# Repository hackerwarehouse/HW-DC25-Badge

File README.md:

# HW-DC25-Badge

This is the project page for the Hacker Warehouse electronic badge that was made for DEF CON 25.

## Background / timeline of badge development

* This was our first attempt at custom hardware / any electronics project at a larger scale
* 2 hardware revisions, 1 silkscreen revision = 3 prototype runs = 4-5 months
* After final board design was obtained, coding started (all code prior was test code to ensure components were working)
* 2 week code sprint before code needed to be frozen for mass badge flashing
* All boards flashed / all components obtained the week of travel of Las Vegas (one final box arrived the day prior to leaving which gave me some anxiety as well)
* 425 badges were produced 

## Badge Specs

* 96×64 Graphic Full Color OLED Display
* 14x Mini NeoPixel RGB LEDs
* ESP8266EX
* 4 tactile buttons arranged in Joypad configuration
* 8 MB Storage
* Powered via 2 AA batteries

## Badge Functions:

* 802.11 channel activity monitor
* Access point scanner
* LED patterns
* OLED animations
* Personalization
* Other useful network tools

## Release Notes
* There was debate if any/all the mischief tools should be included in the badge by default, include it but have them keycode unlockable, or just not include it in stock firmware. Because we know the people working on/in the Black Hat and DEF CON network, along with wanting to have a usable network without causing more issues, the features were not included. 
  * The continued usage of the word 'locked' in all areas made people assume it was all unlockable during the con. We should have chosen different words for the various areas of inclusion. Sorry about that. 

* Multiple reports during DEF CON on wifi functions not working after x usage. Originally suspected it was the sleep/wakeup or disconnect functions not being triggered properly but that doesn't seem to be it. 
  * As previously mentioned, all the badge software was in a two week sprint which didn't leave much or any time for debugging 

* We originally stated source/binaries would be released after the con but because of wifi bug we were wanting to debug and fix it prior to first public release. It seems like people want the code first so we are releasing it as is with the hopes more eyes on it the better and fixes can be submitted. 

## Compiling

These instructions will get you a copy of the project up and running on your local machine.

### Prerequisites

What things you need to install the software and how to install them

```
1. Arduino / compiler
2. Libraries via package manager
  https://github.com/esp8266/Arduino -> http://arduino.esp8266.com/versions/2.3.0/package_esp8266com_index.json
  https://github.com/adafruit/Adafruit_NeoPixel
  https://github.com/kitesurfer1404/WS2812FX
3. Manually copy the two other library packages to Arduino libraries folder
4. 3.3v serial cable
5. and of course a Hacker Warehouse DC25 Badge
```

### Uploading firmware to badge

1. Press / hold the up button on badge
2. Connect 3.3v serial cable
3. Use arduino compile to upload or use other methods such as esptool or esp8266_flasher (with binary file)
  * 115200

## Authors / Contributors

* **Garrett Gee**
* **Jaycon Systems**

## Acknowledgments

* Hat tip to anyone who's code was used
* All the supporters of this project
*

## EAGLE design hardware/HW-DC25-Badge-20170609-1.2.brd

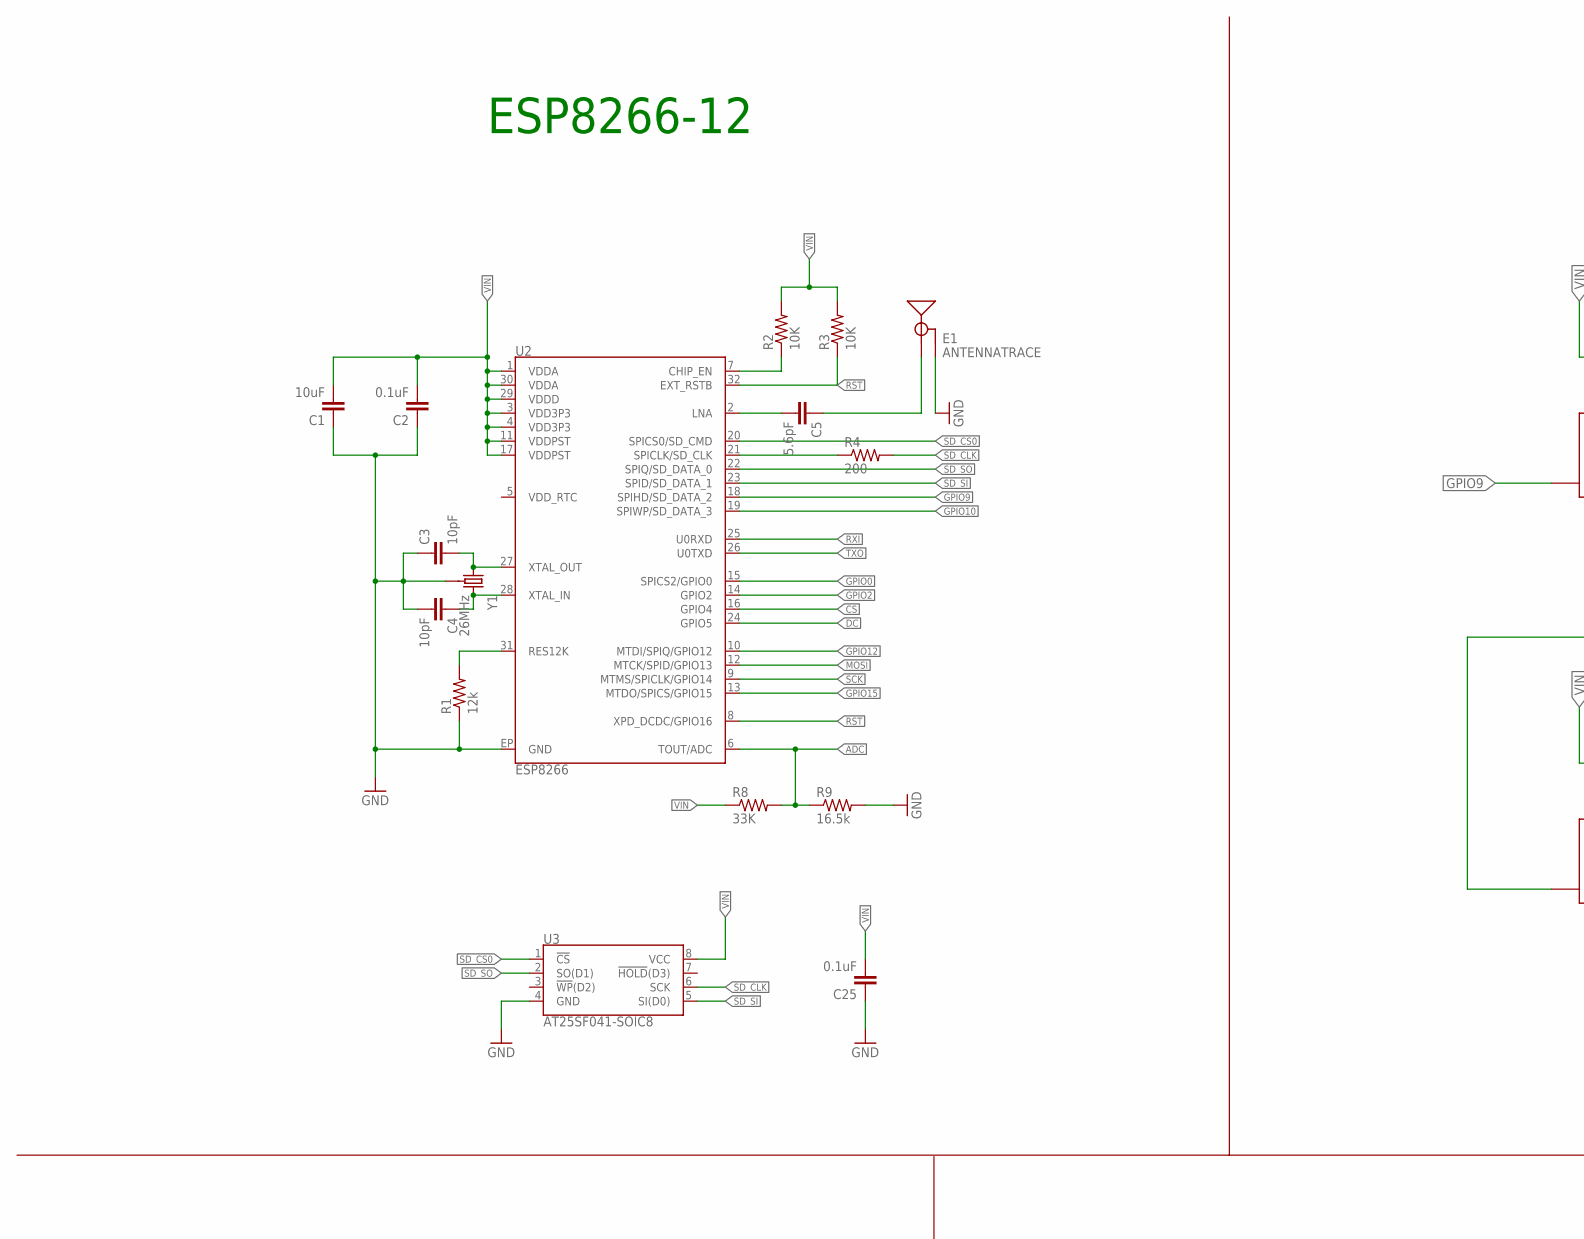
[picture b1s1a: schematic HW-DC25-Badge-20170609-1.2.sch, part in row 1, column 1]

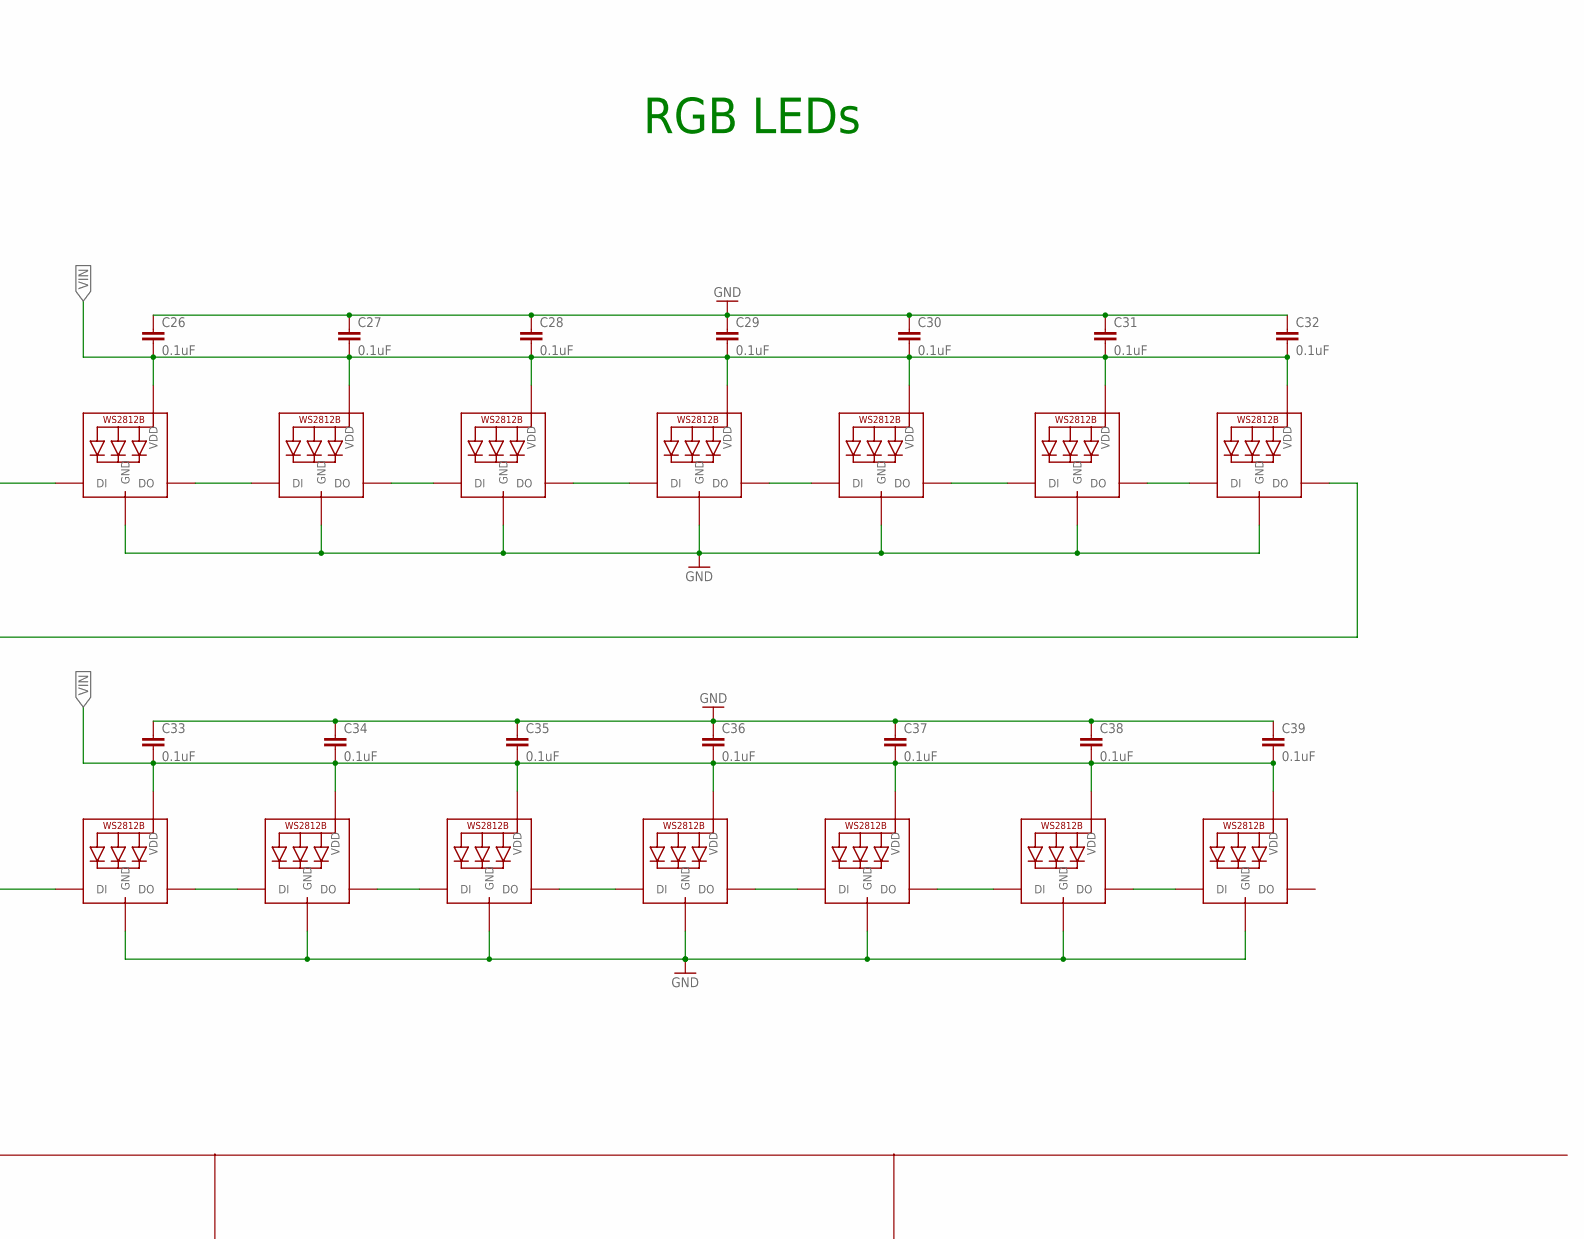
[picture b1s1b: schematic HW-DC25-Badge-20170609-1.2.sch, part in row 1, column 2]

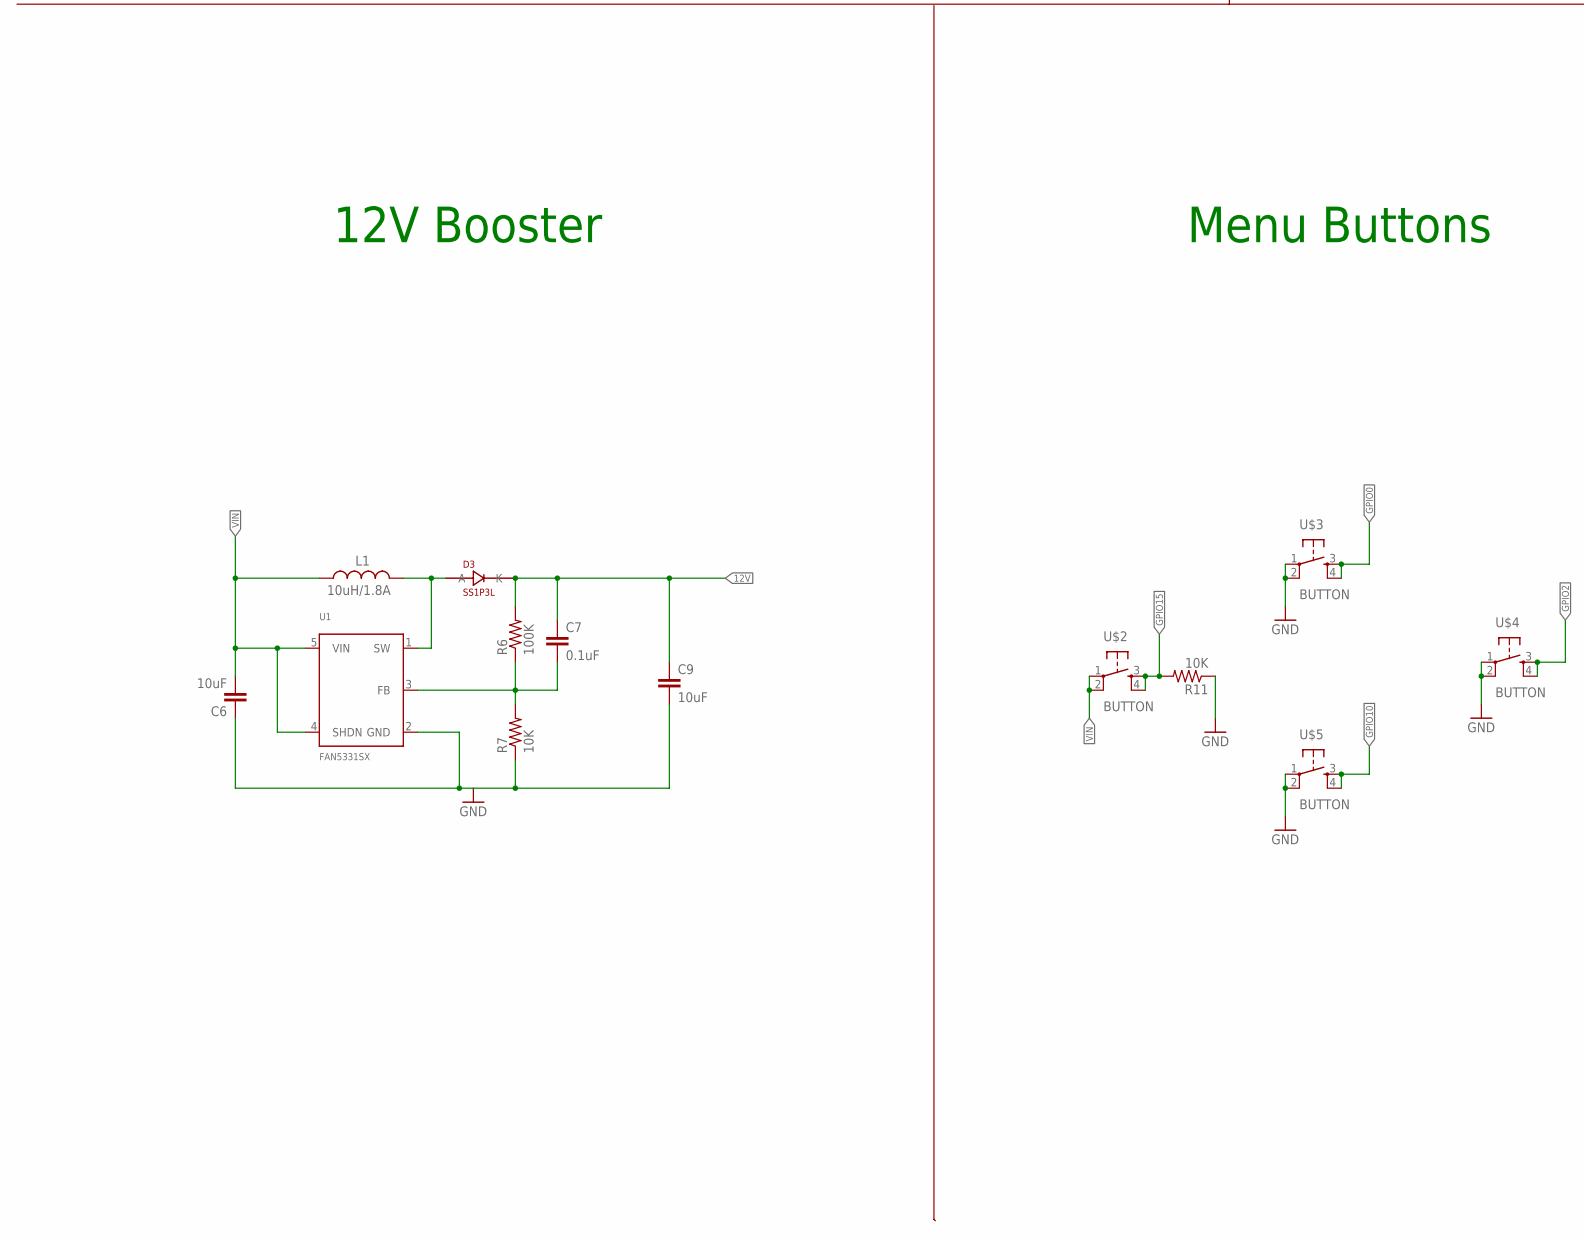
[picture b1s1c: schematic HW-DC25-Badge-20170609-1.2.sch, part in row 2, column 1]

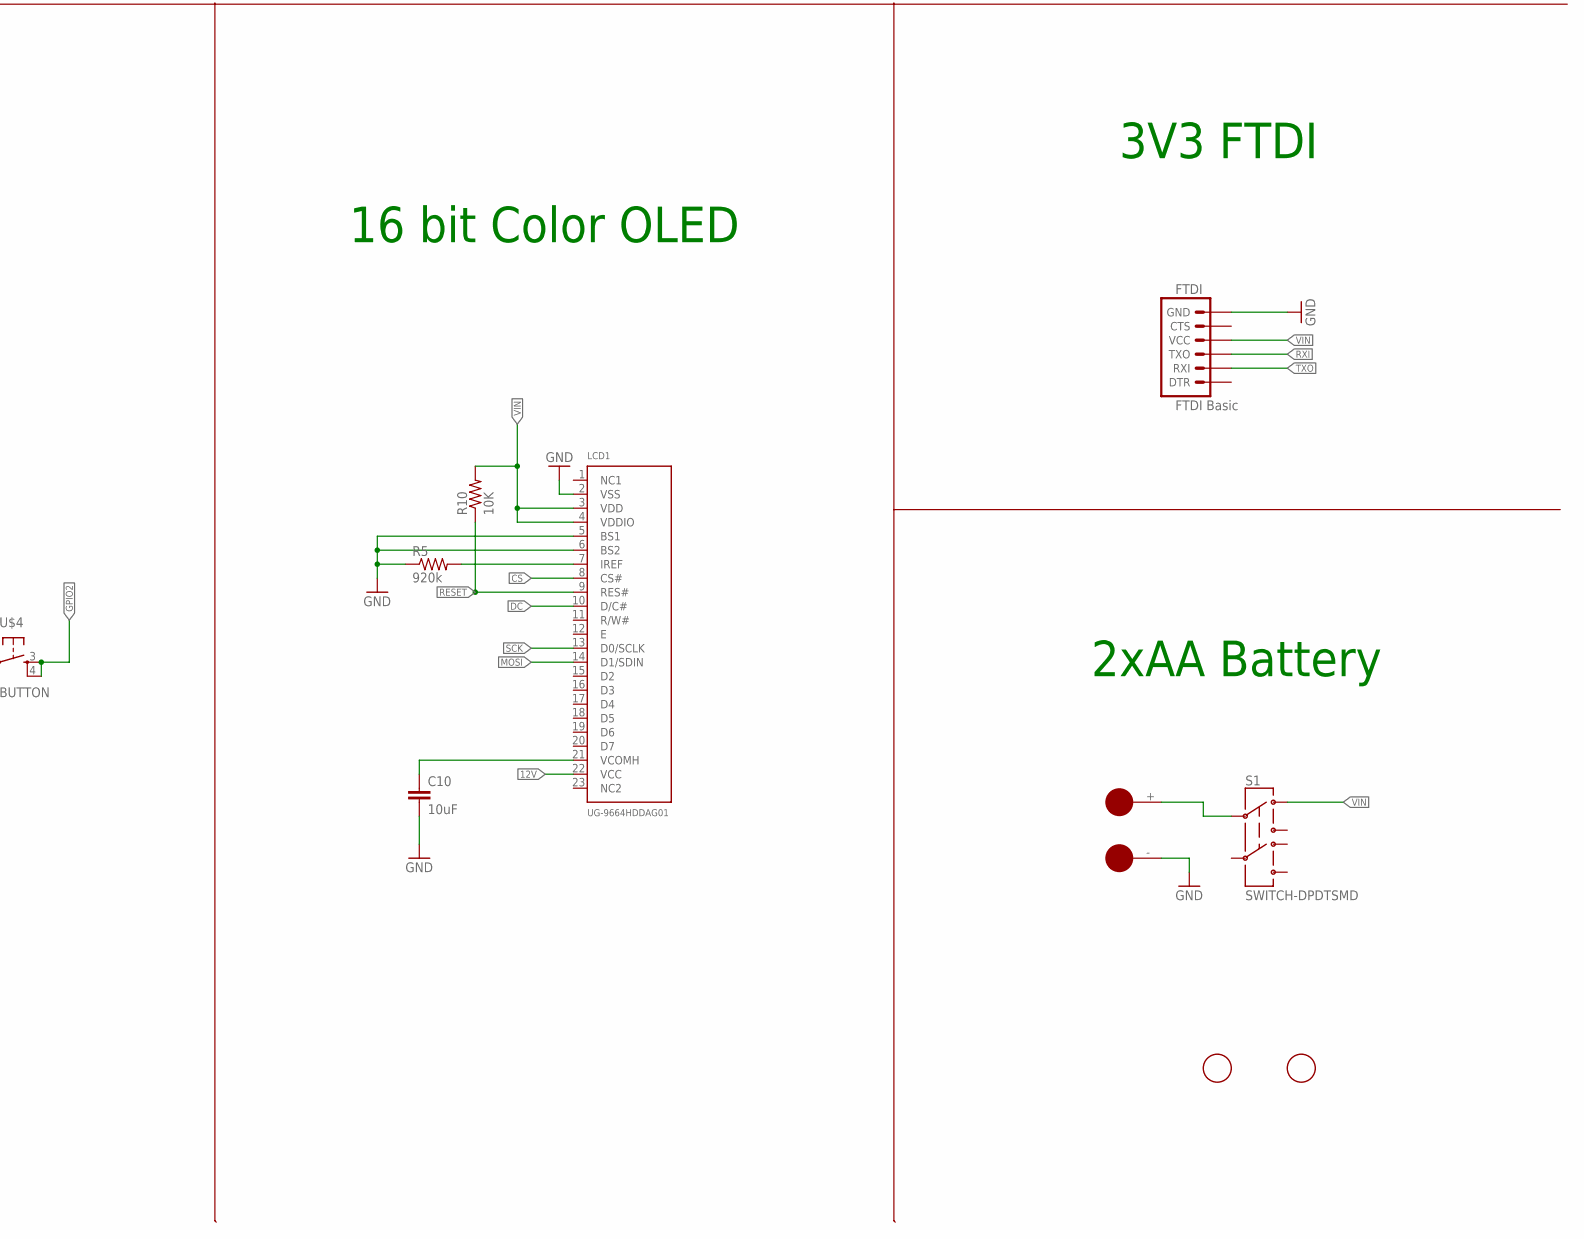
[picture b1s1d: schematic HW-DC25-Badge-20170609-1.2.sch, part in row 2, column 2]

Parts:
C1, C6, C9, C10: 10uF; CAP0603
C2, C7, C25: 0.1uF; CAP0603
C3, C4: 10pF; CAP0603
C5: 5.6pF; CAP0603
C26, C27, C28, C29, C30, C31, C32, C33, C34, C35, C36, C37, C38, C39: 0.1uF; CAP0402
D3: SS1P3L; DO220AAL
E1: ANTENNATRACE; TRACE_ANTENNA_2.4GHZ_25.7MM
FTDI: FTDI Basic; 1X06
L1: 10uH/1.8A; SRU5028
LCD1: UG-9664HDDAG01; UG-9664HDDAG01_WRAPAROUND
LED1, LED2, LED3, LED4, LED5, LED6, LED7, LED8, LED9, LED10, LED11, LED12, LED13, LED14: WS2812B3535; LED3535
R1: 12k; RES-0603
R2, R3, R7, R10, R11: 10K; RES-0603
R4: 200; RES-0603
R5: 920k; RES-0603
R6: 100K; RES-0603
R8: 33K; RES-0603
R9: 16.5k; RES-0603
S1: SWITCH-DPDTSMD; AYZ0202
U1: FAN5331SX; SOT23-5
U2: ESP8266; QFN32
U3: AT25SF041-SOIC8; SO08
U$1: BAT_HOLD; AA
U$2, U$3, U$4, U$5: BUTTON
U$6, U$7: FIDUCIAL; FIDUCIAL_1MM
Y1: 26MHz; CRYSTAL-SMD-3.2X2.5

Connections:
12V: C7.1, C9.1, D3.P$1 (K), LCD1.22 (VCC), R6.2
ADC: R8.2, R9.1, U2.6 (TOUT/ADC)
CS: LCD1.8 (CS#), U2.16 (GPIO4)
DC: LCD1.10 (D/C#), U2.24 (GPIO5)
GND: C1.1, C2.1, C3.1, C4.2, C6.1, C9.2, C10.2, C25.1, C26.P$1 (1), C27.P$1 (1), C28.P$1 (1), C29.P$1 (1), C30.P$1 (1), C31.P$1 (1), C32.P$1 (1), C33.P$1 (1), C34.P$1 (1), C35.P$1 (1), C36.P$1 (1), C37.P$1 (1), C38.P$1 (1), C39.P$1 (1), E1.GND, E1.GND2 (GND), FTDI.6 (GND), LCD1.2 (VSS), LCD1.5 (BS1), LCD1.6 (BS2), LED1.4 (GND), LED2.4 (GND), LED3.4 (GND), LED4.4 (GND), LED5.4 (GND), LED6.4 (GND), LED7.4 (GND), LED8.4 (GND), LED9.4 (GND), LED10.4 (GND), LED11.4 (GND), LED12.4 (GND), LED13.4 (GND), LED14.4 (GND), R1.1, R5.1, R7.1, R9.2, R11.1, U1.2 (GND), U2.EP (GND), U3.4 (GND), U$1.-, U$3.1, U$3.2, U$4.1, U$4.2, U$5.1, U$5.2, Y1.2 (GND), Y1.4 (GND)
GPIO0: U2.15 (SPICS2/GPIO0), U$3.3, U$3.4
GPIO2: U2.14 (GPIO2), U$4.3, U$4.4
GPIO9: LED1.1 (DI), U2.18 (SPIHD/SD_DATA_2)
GPIO10: U2.19 (SPIWP/SD_DATA_3), U$5.3, U$5.4
GPIO12: U2.10 (MTDI/SPIQ/GPIO12)
GPIO15: R11.2, U2.13 (MTDO/SPICS/GPIO15), U$2.3, U$2.4
MOSI: LCD1.14 (D1/SDIN), U2.12 (MTCK/SPID/GPIO13)
unnamed: C3.2, U2.27 (XTAL_OUT), Y1.1
unnamed: C4.1, U2.28 (XTAL_IN), Y1.3 (2)
unnamed: C5.2, U2.2 (LNA)
unnamed: C5.1, E1.ANT (SIGNAL)
unnamed: R1.2, U2.31 (RES12K)
unnamed: R2.1, U2.7 (CHIP_EN)
unnamed: D3.P$2 (A), L1.2, U1.1 (SW)
unnamed: R4.1, U2.21 (SPICLK/SD_CLK)
unnamed: LCD1.7 (IREF), R5.2
unnamed: S1.2, U$1.+
unnamed: C7.2, R6.1, R7.2, U1.3 (FB)
unnamed: C10.1, LCD1.21 (VCOMH)
unnamed: LED1.3 (DO), LED2.1 (DI)
unnamed: LED2.3 (DO), LED3.1 (DI)
unnamed: LED3.3 (DO), LED4.1 (DI)
unnamed: LED4.3 (DO), LED5.1 (DI)
unnamed: LED5.3 (DO), LED6.1 (DI)
unnamed: LED6.3 (DO), LED7.1 (DI)
unnamed: LED7.3 (DO), LED8.1 (DI)
unnamed: LED8.3 (DO), LED9.1 (DI)
unnamed: LED9.3 (DO), LED10.1 (DI)
unnamed: LED10.3 (DO), LED11.1 (DI)
unnamed: LED11.3 (DO), LED12.1 (DI)
unnamed: LED12.3 (DO), LED13.1 (DI)
unnamed: LED13.3 (DO), LED14.1 (DI)
RESET: LCD1.9 (RES#), R10.1
RST: R3.1, U2.8 (XPD_DCDC/GPIO16), U2.32 (EXT_RSTB)
RXI: FTDI.3 (TXO), U2.25 (U0RXD)
SCK: LCD1.13 (D0/SCLK), U2.9 (MTMS/SPICLK/GPIO14)
SD_CLK: R4.2, U3.6 (SCK)
SD_CS0: U2.20 (SPICS0/SD_CMD), U3.1 (!CS!)
SD_SI: U2.23 (SPID/SD_DATA_1), U3.5 (SI(D0))
SD_SO: U2.22 (SPIQ/SD_DATA_0), U3.2 (SO(D1))
TXO: FTDI.2 (RXI), U2.26 (U0TXD)
VIN: C1.2, C2.2, C6.2, C25.2, C26.P$2 (2), C27.P$2 (2), C28.P$2 (2), C29.P$2 (2), C30.P$2 (2), C31.P$2 (2), C32.P$2 (2), C33.P$2 (2), C34.P$2 (2), C35.P$2 (2), C36.P$2 (2), C37.P$2 (2), C38.P$2 (2), C39.P$2 (2), FTDI.4 (VCC), L1.1, LCD1.3 (VDD), LCD1.4 (VDDIO), LED1.2 (VDD), LED2.2 (VDD), LED3.2 (VDD), LED4.2 (VDD), LED5.2 (VDD), LED6.2 (VDD), LED7.2 (VDD), LED8.2 (VDD), LED9.2 (VDD), LED10.2 (VDD), LED11.2 (VDD), LED12.2 (VDD), LED13.2 (VDD), LED14.2 (VDD), R2.2, R3.2, R8.1, R10.2, S1.1, U1.4 (SHDN), U1.5 (VIN), U2.1 (VDDA), U2.3 (VDD3P3), U2.4 (VDD3P3), U2.11 (VDDPST), U2.17 (VDDPST), U2.29 (VDDD), U2.30 (VDDA), U3.8 (VCC), U$2.1, U$2.2

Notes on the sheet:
ESP8266-12
RGB LEDs
12V Booster
Menu Buttons
16 bit Color OLED
3V3 FTDI
2xAA Battery

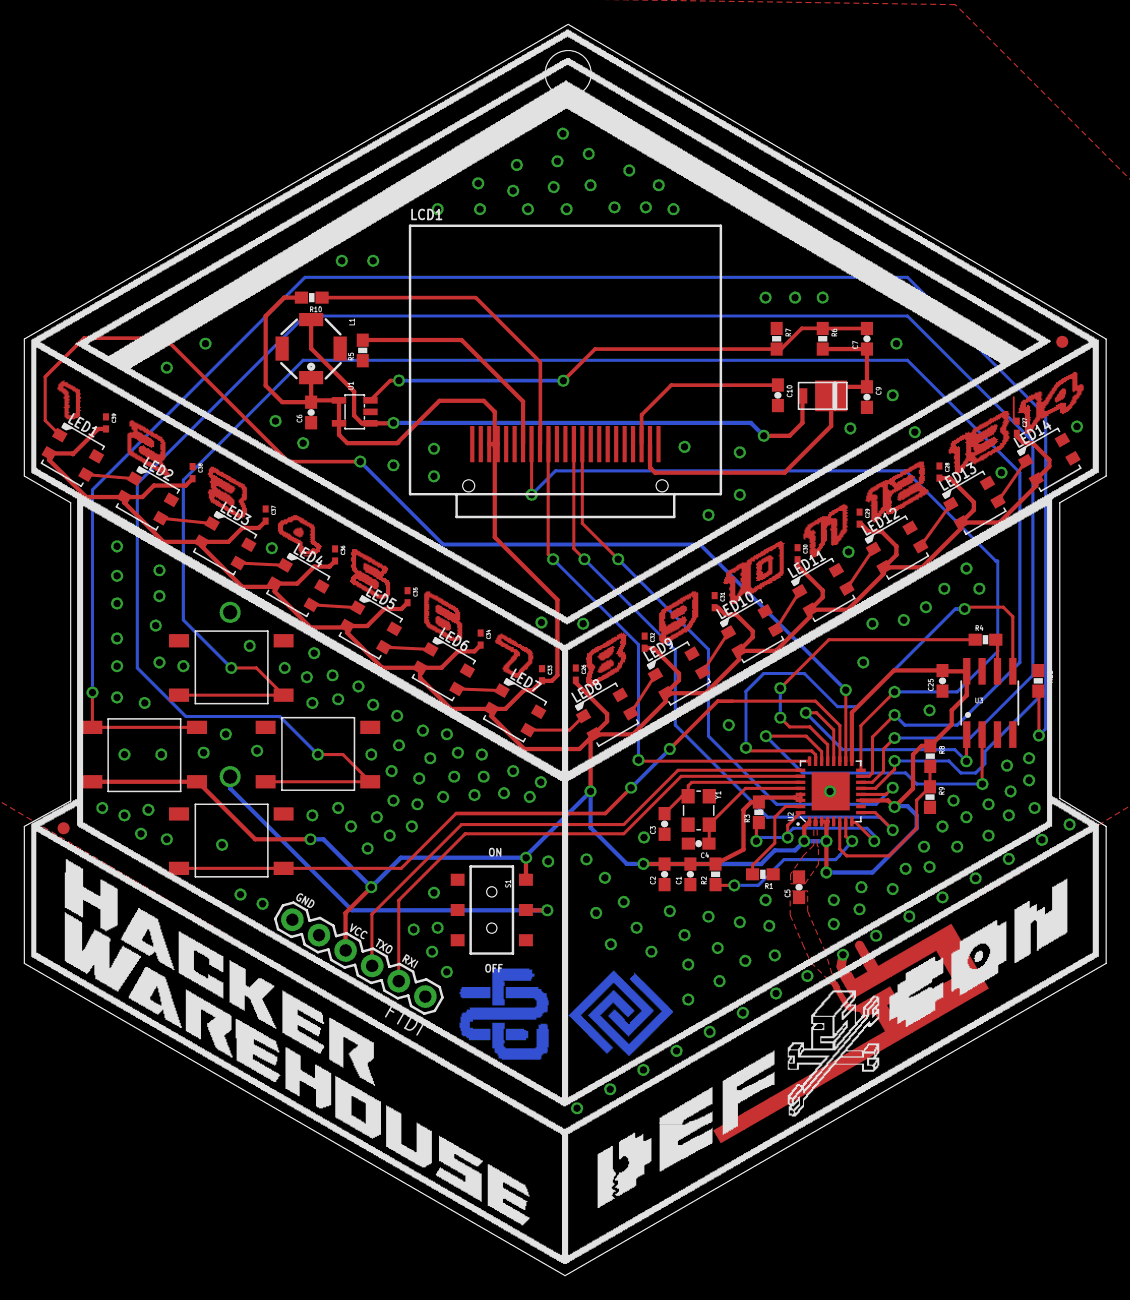
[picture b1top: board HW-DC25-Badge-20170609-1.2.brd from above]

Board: 2 copper layers, 89.5 x 103.5 mm, 66 parts (1 on the bottom side), 46 nets.

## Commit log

2017-06-06 initial checkin
2017-06-06 moved led functions to own file
2017-06-06 moved apscanner to own file
2017-06-07 moved channelactivity to own files
2017-06-07 code cleanup
2017-06-07 sync
2017-06-14 Artwork and battery check features included
2017-06-14 Changed the name of a few submenu titles
2017-06-14 New Artwork
2017-06-14 Artwork and battery features added
2017-06-14 Changed name of few submenu titles
2017-06-15 Added Region Setting feature
2017-06-16 Large images saved in PROGMEM
2017-06-18 menu code cleanup
    - major cleanup of code that drives menu
    - fixed blinky modes to utilize loops
2017-06-18 menu code all updated
    - all main stubs are in place
    - should be much easier to find and add functions now
2017-06-18 minor fixes
    - fixed commenting error
    - changed strings back to PROGMEM
2017-06-18 stable updates
    - added shouts / thanks to early supporters
    - graphics mode - benchmark demo
    - lower default brightness
    - brightness setting function
    - minor code cleanup
2017-06-18 oled brightness settings
    - working now
2017-06-19 led mode updates
    - using WS2812FX library
    - 49 blinky modes total currently
    - kept our original sample code for reference
    - renamed counter to btncounter
2017-06-19 about info updates
    - hwinfo added
    - changed structure of print of text
2017-06-19 first draft
2017-06-19 updates
    - client tools menu
    - more strings to flash
2017-06-19 minor correction
2017-06-22 optimizations
    - blinky favorites order improved
    - changed order of blinky menu
    - added appmode button menu bypass
    - adopted shouts function to new appmode function. much improved
    - artwork images
2017-06-24 persistent settings
    - brightness settings
    - region settings
    - channel activity uses region settings
2017-06-24 settings to own file
    - SaveBrightness moved
2017-06-24 display brightness setting kludge
    brightness not consistent across menu system. manually set brightness on each change
2017-06-24 artwork
    - persistent setting of saved artwork
    - 3 options currently
    - renamed small artwork used in credits
2017-06-24 artwork display cleanup
2017-06-24 moved loadSettings to settings file
2017-06-24 art optimizations
    - all artwork in flash
    - new artwork
2017-06-24 blinky optimization
    - local variable not global
    - byte instead of int
2017-06-24 minor fix
2017-06-25 code cleanup
    - changed id to btnid to be more clear
2017-06-25 flashlight brightness toggle
2017-06-25 minor optimization
2017-06-25 button echo
    - function works itself
    - doesn't trigger anything so it is more for future references
2017-06-25 unlocks
    - region working
    - reorganize menu
2017-06-25 minor cleanup
2017-06-26 channel activity / channel usage
    - renamed JS channel activity to channel usage as it is a better title match
    - created channel activity packet monitor tool via monitor mode
    - minor bugs in new channel activity app but main parts work
    - commented out all the forceSleepBeing and forceSleepWake calls. too many issues with this right now
2017-06-26 name updates
2017-06-28 core cleanup
2017-06-28 wifi updates
    - ap scanner much improved
    - renamed channel activity to packet monitor
    - adjusted region setting for perma unlock
2017-06-29 organization / cleanup
    - moved shouts to about
    - moved benchmark to graphics
    - moved artwork to graphics
    - moved button echo to extras
    - added keyboard demo to extras
    - re-organized menu
2017-06-30 misc
    - version update
    - code cleanup
2017-07-01 deauth code
    - renamed pktmonitor to packetpower
    - which includes packet monitor and deauth monitor and detector functions currently
    - fixed menu order
2017-07-01 stubs
2017-07-01 client beacon sniffer
    - initial poc working
2017-07-01 3d cube demo
2017-07-01 graphic demos
    - gauge
    - clock
2017-07-01 point release
2017-07-01 snake game
2017-07-01 char bug fix
2017-07-03 bug fix / code cleanup
    - fixed channel 1 display bug
    - removed led flasher code - was distracting
2017-07-03 settings stub
2017-07-03 removed wifimanager
    - not stable enough
    - not flexible enough
    - need to build own version
2017-07-04 open ap scanner
2017-07-04 minor tweaks
2017-07-04 client menu
    - removed for now. lacking time before code freeze
    - kept stubs in for future
2017-07-05 freeze for release
    - no foxhunt
    - rearranged packet code for organization
2017-07-05 binary releases
2017-07-05 menu fix
2017-08-08 public sync
2017-08-08 hardware source files sync

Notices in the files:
parts and their libraries:
Jaycon OPL Capacitors: Licensing: Creative Commons ShareAlike 4.0 International - https://creativecommons.org/licenses/by-sa/4.0
